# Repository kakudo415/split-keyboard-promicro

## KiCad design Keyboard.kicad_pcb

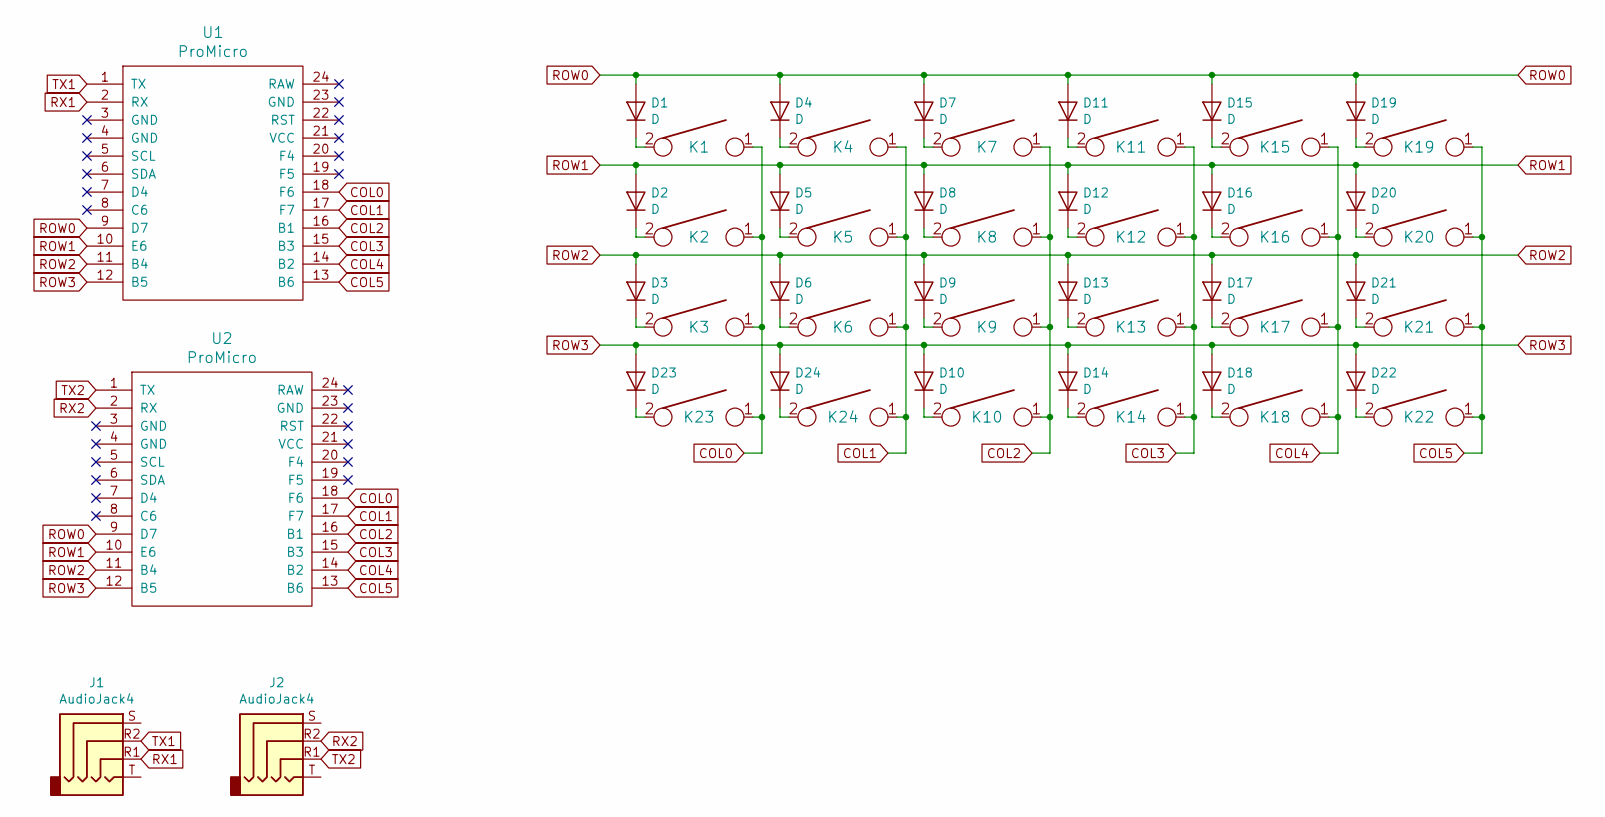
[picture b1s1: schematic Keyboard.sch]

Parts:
D1, D2, D3, D4, D5, D6, D7, D8, D9, D10, D11, D12, D13, D14, D15, D16, D17, D18, D19, D20, D21, D22, D23, D24: D; D_DO-35_SOD27_P7.62mm_Horizontal
J1, J2: AudioJack4; Jack_3.5mm_PJ320E_Horizontal
K1, K2, K3, K4, K5, K6, K7, K8, K9, K10, K11, K12, K13, K14, K15, K16, K17, K18, K19, K20, K21, K22, K23, K24: KEYSW; SW_Cherry_MX1A_1.00u_Plate
U1, U2: ProMicro

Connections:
COL0: K1.1, K2.1, K3.1, K23.1, U1.18 (F6), U2.18 (F6)
COL1: K4.1, K5.1, K6.1, K24.1, U1.17 (F7), U2.17 (F7)
COL2: K7.1, K8.1, K9.1, K10.1, U1.16 (B1), U2.16 (B1)
COL3: K11.1, K12.1, K13.1, K14.1, U1.15 (B3), U2.15 (B3)
COL4: K15.1, K16.1, K17.1, K18.1, U1.14 (B2), U2.14 (B2)
COL5: K19.1, K20.1, K21.1, K22.1, U1.13 (B6), U2.13 (B6)
unnamed: D1.1 (K), K1.2
unnamed: D2.1 (K), K2.2
unnamed: D3.1 (K), K3.2
unnamed: D4.1 (K), K4.2
unnamed: D5.1 (K), K5.2
unnamed: D6.1 (K), K6.2
unnamed: D7.1 (K), K7.2
unnamed: D8.1 (K), K8.2
unnamed: D9.1 (K), K9.2
unnamed: D10.1 (K), K10.2
unnamed: D11.1 (K), K11.2
unnamed: D12.1 (K), K12.2
unnamed: D13.1 (K), K13.2
unnamed: D14.1 (K), K14.2
unnamed: D15.1 (K), K15.2
unnamed: D16.1 (K), K16.2
unnamed: D17.1 (K), K17.2
unnamed: D18.1 (K), K18.2
unnamed: D19.1 (K), K19.2
unnamed: D20.1 (K), K20.2
unnamed: D21.1 (K), K21.2
unnamed: D22.1 (K), K22.2
unnamed: D23.1 (K), K23.2
unnamed: D24.1 (K), K24.2
ROW0: D1.2 (A), D4.2 (A), D7.2 (A), D11.2 (A), D15.2 (A), D19.2 (A), U1.9 (D7), U2.9 (D7)
ROW1: D2.2 (A), D5.2 (A), D8.2 (A), D12.2 (A), D16.2 (A), D20.2 (A), U1.10 (E6), U2.10 (E6)
ROW2: D3.2 (A), D6.2 (A), D9.2 (A), D13.2 (A), D17.2 (A), D21.2 (A), U1.11 (B4), U2.11 (B4)
ROW3: D10.2 (A), D14.2 (A), D18.2 (A), D22.2 (A), D23.2 (A), D24.2 (A), U1.12 (B5), U2.12 (B5)
RX1: J1.R1, U1.2 (RX)
RX2: J2.R2, U2.2 (RX)
TX1: J1.R2, U1.1 (TX)
TX2: J2.R1, U2.1 (TX)

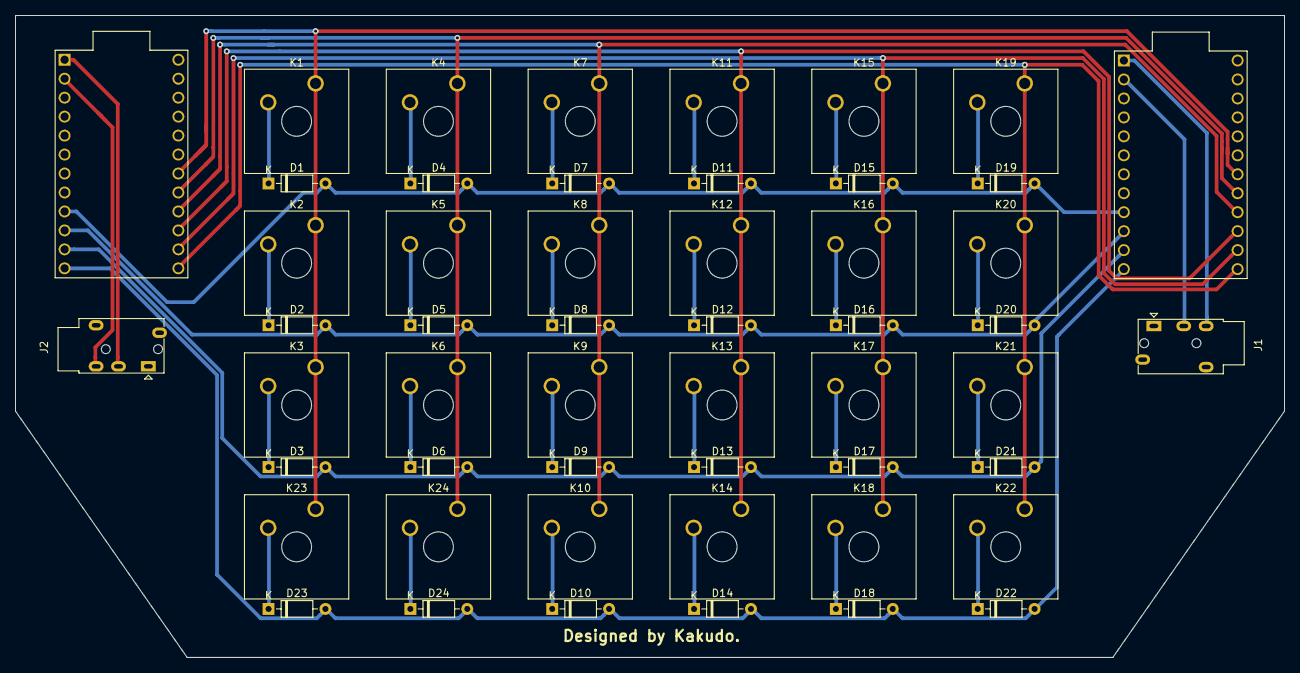
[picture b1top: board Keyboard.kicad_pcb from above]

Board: 2 copper layers, 170.0 x 86.0 mm, 52 parts (0 on the bottom side), 38 nets.

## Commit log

2019-03-09 firmware
